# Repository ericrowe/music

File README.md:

# Music Fabrication & Band Prop Engineering Repository

This umbrella repository supports independent music fabrication, 3D parametric CAD modeling, and controlled engineering documentation for musical instruments, accessories, and competitive field marching band props.

---

## 🎺 Subprojects Overview

### 1. Pine Creek High School Marching Band (PCHSMB)

Prop engineering, fabrication guides, and volunteer field operations for the Pine Creek High School Marching Band (Colorado Springs, CO):

| Subproject | Description | Key Deliverables & Manuals |
|---|---|---|
| [**2026 Production: *Continuum***](PCHSMB/2026%20Continuum/) | Master competition day field operations guide coordinating all 35 props (16 Duck Blinds, 11 Backdrops, 4 Stages + 4 Staircases). | • [`Continuum_2026_Prop_Operations_Guide.pdf`](PCHSMB/2026%20Continuum/Continuum_2026_Prop_Operations_Guide.pdf) (15 pp)<br>• NFHS High School & NCAA College field coordinate maps & pocket cards<br>• Wind safety NO-GO threshold (>20 mph) & operational weather briefings |
| [**Rolling Backdrops**](PCHSMB/_Backdrop/) | 11 modular 10 ft H × 8 ft W visual displays on heavy-duty 2x4 rolling carts with 60" mid rails and 3/4" iron wing ballast posts. | • [`Backdrop_Assembly_Guide.pdf`](PCHSMB/_Backdrop/docs/Backdrop_Assembly_Guide.pdf) (Release v0 (D9), 28 pp)<br>• Semicircular wind relief flaps ($R=4.0"$, $8" \times 4"$, 8-flap 3-2-3 primary layout)<br>• Frame CAD, drill alignment jigs & substrate trade study (`TS-BDP-2026-02`) |
| [**Sideline Screens ("Duck Blinds")**](PCHSMB/_Sideline%20Screen/) | 16 folding 4 ft H × 8 ft W front sideline concealers in 3/4" EMT conduit; folds coplanar to $< 2.0"$. | • [`Sideline_Screen_Duck_Blind_Build_Instructions.pdf`](PCHSMB/_Sideline%20Screen/docs/Sideline_Screen_Duck_Blind_Build_Instructions.pdf) (Release v0 (D34), 27 pp)<br>• Two-Student Direct Carry protocol (zero carts)<br>• Semicircular wind relief flaps ($R=4.0"$, 6 flaps) & universal corner protectors |
| [**Performance Stages & Staircases**](PCHSMB/_Stages/) | 4 modular rolling performance stages (8 half-units) and 4 mobile staircases with flush 6.0" inter-section gap bridges. | • [`Stage_Platform_Build_Instructions.pdf`](PCHSMB/_Stages/docs/Stage_Platform_Build_Instructions.pdf) (Release v0 (D1), 11 pp)<br>• 6.0" Inter-Section Gap Bridge Analysis (`TR-STG-2026-01`)<br>• Shaded Lighting Scaffolding Pavilion Trade Study (`TS-STG-2026-02`) |
| [**Universal Field Prop Lighting Platform**](PCHSMB/_Lighting%20Controller/) | Enduring, show-agnostic 915 MHz Sub-GHz wireless lighting control ecosystem (Synapse Pit Master Console & Peripheral Prop Nodes). | • Systems Requirements ([`REQUIREMENTS.md`](PCHSMB/_Lighting%20Controller/docs/REQUIREMENTS.md)) & Schematics ([`CARRIER_BOARD_SCHEMATICS.md`](PCHSMB/_Lighting%20Controller/docs/CARRIER_BOARD_SCHEMATICS.md))<br>• KiCad carrier boards, Pilot & 30-Prop BOM Guides, & zero-code CSV show workflow<br>• HTML5 Field Show Simulator & Prop Power Calculator |
| [**Technical Reports & Concept Planning**](PCHSMB/TECHNICAL_REPORTS_REGISTRY.md) | Master engineering registry (`TR`/`TS`/`SPEC`/`DIR`), 2027 Prop Ecosystem Executive Menu, and Director's Briefing Deck. | • [`TECHNICAL_REPORTS_REGISTRY.md`](PCHSMB/TECHNICAL_REPORTS_REGISTRY.md)<br>• [`PCHSMB/docs/`](PCHSMB/docs/) |
| **Legacy & Research** | Historical show props, mechanical flag launchers, and kinetic mechanisms. | • [`PCHSMB/2023 Firebird/`](PCHSMB/2023%20Firebird/), [`2024 Medusa/`](PCHSMB/2024%20Medusa/), [`2025 Valkyrie/`](PCHSMB/2025%20Valkyrie/)<br>• [`PCHSMB/Experiments/Flag Launcher/`](PCHSMB/Experiments/Flag%20Launcher/) & [`Kinetics/`](PCHSMB/Experiments/Kinetics/) |

---

### 2. Instrument Accessories & Workshop Projects

| Project | Description | Primary Materials / Formats |
|---|---|---|
| [**Standcessories**](Standcessories/) | Stand-mounted accessories (mute holders, pencil clips, tablet mounts) engineered for Manhasset #48 music stands. | FreeCAD (`.FCStd`), 3MF slicer files, Black PETG/PLA |
| [**Trumpet**](Trumpet/) | Trumpet mutes (straight, cup, practice), Jo-Ral mute replacement caps, mouthpiece holders, and lyres. | FreeCAD (`.FCStd`), 3MF slicer files, 3D printed acoustics |
| [**Flutes**](Flutes/) | Wall mounts, display fixtures, and stands for Native American and concert flutes. | FreeCAD (`.FCStd`), 3MF slicer files |
| [**Baritone**](Baritone/) & [**Horn**](Horn/) | Replacement valve finger buttons and instrument-mounted pencil clips. | FreeCAD (`.FCStd`), 3MF slicer files, STL meshes |
| [**Luggage Tags**](Luggage%20Tags/) | Personalized, durable instrument case luggage tags. | 3D printed TPU (flexible) |

---

## 📐 Repository Standards & AI Agent Guidelines

Authoritative engineering and documentation rules are codified in:
- [**`AGENTS.md`**](AGENTS.md): Universal cross-agent architecture, document registries, and cross-project synchronization rules.
- [**`GEMINI.md`**](GEMINI.md): Antigravity / Gemini CLI adapter.

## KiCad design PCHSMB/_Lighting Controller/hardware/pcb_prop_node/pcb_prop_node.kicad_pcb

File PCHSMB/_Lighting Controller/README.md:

# PCHSMB Universal Field Prop Lighting Control System

The **PCHSMB Universal Field Prop Lighting Control System** is an enduring, show-agnostic field electronics and wireless lighting platform engineered for the Pine Creek High School Marching Band. It replaces single-use, ad-hoc wiring rigs with a standardized, modular infrastructure capable of synchronizing dynamic visual illumination across up to 64 independent field props (including rolling backdrops, sideline screens, performance stages, soloist platforms, kinetic props, and field tarps) on a regulation outdoor football stadium.

The system is decoupled from any single competitive production. Future band productions can completely reprogram all lighting cues, color schemes, dynamic chases, groupings, and downbeat triggers each season **without requiring software development, command-line tools, firmware compilation, or artificial intelligence prompting**.

---

## 1. System Architecture & Signal Flow

```
===================================================================================================
                                      SYSTEM SIGNAL FLOW & TOPOLOGY
===================================================================================================

[NON-TECHNICAL SHOW AUTHORING]
Band Directors & Students edit show_cues.csv in Microsoft Excel / Google Sheets
                                  │
                                  ▼
[ZERO-CODE SHOW DEPLOYMENT]
  Method A: Drag-and-drop onto Synapse USB Drive ("PCHSMB_LIGHT")
  Method B: Connect smartphone/tablet to Synapse Wi-Fi Portal (http://192.168.4.1/)
                                  │
                                  ▼
┌─────────────────────────────────────────────────────────────────────────────────────────────────┐
│ SYNAPSE PIT MASTER CONSOLE (PCB-SYNAPSE-V1)                                                    │
│ • Front-Ensemble Tabletop Console (Pit Cart Accessory Rail Mount)                               │
│ • 16x 16mm Rugged Momentary Pushbuttons (Screw-Clamp Terminals, Zero Solder)                    │
│ • Dedicated Emergency Blackout E-Stop (Hardware Priority Interrupt)                            │
│ • Rotary Parameter Encoder + 128x64 Sunlight-Readable OLED Status Display                       │
│ • 3.5mm Isolated SMPTE LTC / Audio Click Track Line-In                                         │
│ • Dual-Source OR-ed Power Bus (5V USB + 7-18V Auxiliary DC)                                     │
│ • 902–928 MHz Sub-GHz ISM Broadcast Master (Semtech SX1262 Transceiver, RP-SMA Antenna)         │
└────────────────────────────────────────────────┬────────────────────────────────────────────────┘
                                                 │
                                                 │ 902–928 MHz Wireless Broadcast Link (Clock Sync & Cue Downbeats)
                                                 │ Master Millisecond Timecode Heartbeat + Event Triggers
                                                 │ Phase-Lock Jitter ≤ 2.0 ms | Slant Range ≥ 150 m | Zero Central Streaming
                                                 │
                                                 ▼
┌─────────────────────────────────────────────────────────────────────────────────────────────────┐
│ PERIPHERAL PROP RECEIVER & LED DRIVER (PCB-PROP-NODE-V1) [FLEET: 1 TO 256 PROPS]               │
│ • Deployed Inside Field Props (Backdrops, Sideline Screens, Soloist Platforms, Star Tarps)     │
│ • Standard Commercial Tool Battery Input (Milwaukee M18 / DeWalt 20V, 15V–21V DC)              │
│ • High-Efficiency 5.0V / 8.0A Continuous Synchronous Buck Regulator                            │
│ • Hardware Reverse-Polarity P-FET + Hardware 15.0V Undervoltage Lockout (UVLO)                  │
│ • 8-Bit Hardware DIP Switch Bank (Unique Device Hardware Serial ID 0–255 / 0x00–0xFF)           │
│ • Distributed Timeline Engine: Autonomous Flash Cues on 40 MHz Quartz Oscillator Time           │
│ • Loss-of-Signal Immunity: Uninterrupted local cue execution (crystal drift < 15ms over 12 min) │
│ • Spare Remap: Wi-Fi OTA off-field or < 100ms emergency 915 MHz profile push from Synapse     │
│ • Quad-Channel 5.0V CMOS Level Shifter (74AHCT125) with 33Ω Transmission Line Resistors        │
└────────────────────────────────────────────────┬────────────────────────────────────────────────┘
                                                 │
                                                 ▼ 4x High-Speed Damped Parallel Data Lines (5V)
┌─────────────────────────────────────────────────────────────────────────────────────────────────┐
│ PROP LED FIXTURES & SURFACE ARRAYS                                                             │
│ Channel 1: Primary Outline / Perimeter Rail Extrusion (WS2812B / SK6812 / APA102)               │
│ Channel 2: Secondary Accent / Kinetic Graphic Trim                                             │
│ Channel 3: Downward Stage Deck Wash / Soloist Core Luminaire                                   │
│ Channel 4: Ground Runner / Ancillary Ribbon / Auxiliary Luminaire                              │
└─────────────────────────────────────────────────────────────────────────────────────────────────┘
===================================================================================================
```

---

## 2. Subsystem Directory Structure

```
_Lighting Controller/
├── IDEAS.md                              # Project Inbox & Engineering Backlog (HitL Workflow)
├── docs/                                 # Controlled Documentation & Schematics
│   ├── REQUIREMENTS.md                   # Authoritative Systems Requirements (INCOSE / ISO 29148)
│   ├── CARRIER_BOARD_SCHEMATICS.md       # Electrical Schematics, Pinouts & Netlists
│   ├── Lighting_Controller_Pilot_Build_BOM.pdf   # 1 Synapse + 3 Peripherals Pilot Procurement Guide
│   ├── Carrier_Board_BOM_Purchasing_Guide.pdf    # Full Fleet 30-Prop Purchasing Schedule
│   ├── project.json                      # Controlled Document Build Manifest
│   ├── AGENTS.md                         # Subproject Engineering Instructions
│   └── images/                           # High-Resolution 3D PCB Previews & Visuals
│
├── hardware/                             # Master CAD, KiCad & PCB Fabrication
│   ├── pcb_synapse_controller/           # Synapse Carrier Board KiCad Project (ERC/DRC 0 Errors)
│   ├── pcb_prop_node/                    # Prop Node Carrier Board KiCad Project (ERC/DRC 0 Errors)
│   └── build_kicad_carrier_boards.py     # Pure-Python Parametric KiCad Generator & DRC Runner
│
├── firmware/                             # Microcontroller Software & Protocol Stack
│   └── README.md                         # Dual-Core ESP32-S3 Tasking, 915 MHz Framing & DMA Engine
│
└── software/                             # Show Reprogramming & Zero-Code Authoring Suite
    ├── README.md                         # Non-Technical Authoring & Ingestion Guide
    ├── show_cues_template.csv            # Master CSV Show Cue Template (Excel / Sheets Friendly)
    └── PCHSMB_Show_Simulator.html        # Interactive Zero-Install HTML5 Field Visualizer & Validator
```

---

## 3. Hardware Subsystem Specifications

### A. Synapse Pit Master Console (`PCB-SYNAPSE-V1`)
* **Form Factor:** Compact tabletop aluminum console clamped to a front-ensemble keyboard or percussion rack rail on the front sideline.
* **Operator Interface:** 16 discrete, heavy-duty $16\,\text{mm}$ IP67 metal momentary pushbuttons arranged for two-handed fingertip triggering by a gloved student musician.
* **Zero-Solder Field Wiring:** All 16 pushbuttons connect to the carrier board via high-retention $5.08\,\text{mm}$ screw-clamp terminal blocks (`J5` and `J6`).
* **Emergency Blackout (E-Stop):** Dedicated 2-pin screw terminal (`J7`) routed to a high-priority hardware interrupt, transmitting a preemptive visual blackout packet across the entire field in $T \le 5.0\,\text{ms}$.
* **Navigation & Feedback:** 24-detent continuous rotary encoder with push switch, paired with a $128 \times 64$ sunlight-readable monochrome OLED display.
* **Audio Synchronization:** Isolated $3.5\,\text{mm}$ line-in jack for SMPTE LTC timecode or front ensemble audio click track pulse detection.
* **Dual Power OR-ing:** Operates seamlessly from either $5.0\,\text{V}$ USB or auxiliary $7.0\,\text{V}\text{–}18.0\,\text{V}$ DC with zero brownout or MCU reset when switching sources.
* **Wireless Transceiver:** Heltec V3 ESP32-S3 module with Semtech SX1262 LoRa/FSK transceiver, outputting $+22\,\text{dBm}$ into a chassis-mounted RP-SMA whip antenna.

### B. Peripheral Prop Receiver & Driver Node (`PCB-PROP-NODE-V1`)
* **Deployment:** Sealed inside weather-resistant 3D-printed enclosures mounted to field props (Rolling Backdrops, Sideline Screens, Soloist Stages, Star Tarps).
* **Power Source:** Universal commercial $18\,\text{V}$ tool battery packs (DeWalt 20V Max / Milwaukee M18, $15.0\,\text{V}\text{–}21.0\,\text{V}$ DC).
* **Step-Down Power Conversion:** Finned waterproof synchronous buck regulator delivering $5.0\,\text{V} \pm 0.15\,\text{V}$ DC regulated at up to $20.0\,\text{A}$ continuous ($100\,\text{W}$, $\ge 95\%$ efficiency).
* **Battery Protection & Safety:**
  - Hardware P-channel power MOSFET reverse-polarity protection ($V_{\text{drop}} \le 40\,\text{mV}$, survives $-24\,\text{V}$ DC indefinitely).
  - Hardware Undervoltage Lockout (UVLO) disconnecting load at $V_{\text{bat}} \le 14.8\,\text{V}$ to prevent permanent lithium cell damage.
* **Parallel Multi-Zone Driving:** Quad $5.0\,\text{V}$ CMOS level-shifted push-pull channels (`74AHCT125`) with $33\,\Omega$ series transmission line resistors, driving up to $5.0\,\text{m}$ of external cable without edge ringing.
* **8-Bit Hardware DIP Switch Bank (`SW1`):** 8-position slide DIP switch providing 256 unique hardware device serial numbers (`0`–`255` / `0x00`–`0xFF`). Decouples physical hardware serial from software show configuration.

### C. Distributed Autonomous Timeline & Quartz Phase-Locking Architecture
* **Autonomous Local Show Engines:** Each prop node functions as an independent animation engine executing its scheduled cue timeline from onboard SPI flash memory. Every unit runs identical precompiled firmware, but executes its unique assigned timeline profile (e.g., Unit 4 triggers Cue 3 at $18.43\,\text{s}$ with a 2-second cyan bloom, while Unit 12 triggers Cue 3 at $20.15\,\text{s}$ with a radial chase).
* **915 MHz Millisecond Clock-Sync Heartbeat:** The Sub-GHz broadcast link does **not** stream raw pixel frames and is **not** a single point of failure. It periodically transmits an unacknowledged elapsed millisecond timecode packet (`uint32_t master_ms`).
* **Loss-of-Signal Immunity:** Local prop timing is clocked by the Heltec V3's onboard $40\,\text{MHz}$ quartz crystal oscillator. If RF communication is momentarily shadowed by stadium structures or drops out entirely, **animations do not freeze or halt**. The node continues executing its timeline on quartz crystal time with $< 15\,\text{ms}$ total drift over a 12-minute field show. When the 915 MHz signal is re-established, a Phase-Locked Loop (PLL) slews the local millisecond clock seamlessly back into sub-frame synchronization.
* **Spare Unit Replacement & Re-mapping Workflow:** If a field prop (e.g., Unit 4) suffers mechanical or electrical damage on the sideline and spare Unit 18 is deployed:
  1. *Off-Field / Rehearsal Re-mapping:* Connect to Unit 18 via Wi-Fi OTA portal (or local staging router) and select "Assign Profile: Prop 4". The complete 272-byte timeline profile is flashed to Unit 18 in $< 2.0\,\text{s}$.
  2. *On-Field Emergency Re-mapping:* From the Synapse pit master console OLED rotary menu, select `SPARE REMAP: HW18 -> PROP 4`. Synapse broadcasts a high-priority 915 MHz configuration packet re-mapping Unit 18's DIP serial to Prop 4's timeline profile in $< 100\,\text{ms}$ without requiring laptops, Wi-Fi networks, or physical disassembly.

---

## 4. The Zero-Code Show Reprogramming Suite

High school marching band staff change from season to season. The PCHSMB platform enforces a strict **Zero-Software & Zero-AI Reprogramming Mandate** (**`REQ-SW-01`**):

1. **Spreadsheet Authoring:** Directors and visual coordinators edit cues in [`software/show_cues_template.csv`](software/show_cues_template.csv) using **Microsoft Excel, Google Sheets, or Apple Numbers**.
2. **Instant Browser Testing:** Double-clicking [`software/PCHSMB_Show_Simulator.html`](software/PCHSMB_Show_Simulator.html) opens an interactive 2D football field simulator in any browser. Users drag and drop their CSV file to validate syntax and test cues 1–16 on a virtual field grid in real-time.
3. **Plug-and-Play Loading:**
   - **Method A (USB Flash Drive):** Connect Synapse to any computer via USB-C. Drag and drop `show_cues.csv` onto the `PCHSMB_LIGHT` drive. Synapse validates the file upon eject and flashes its memory.
   - **Method B (Rehearsal Web Engine & LoRa-Orchestrated Wi-Fi):** During practices on shore power, an optional integrated Raspberry Pi and travel router host a full browser dashboard, waking up fleet prop Wi-Fi on demand via a LoRa command packet for zero-touch Over-The-Air show updates across all 30+ field props (see [`IDEAS.md`](IDEAS.md) — Idea 001).
4. **Error Protection:** Typos in Excel generate an immediate plain-English report (`error_log.txt` and OLED notification) pinpointing the exact row and column without crashing the system.

---

## 5. Procurement & Budget Schedules

| Scope | Assemblies Included | Estimated Total Cost | Status / Procurement Guide |
|---|---|:---:|---|
| **Pilot Bench Kit** | 1 Synapse Master + 3 Prop Nodes (4-Node Test Mesh) | **$332.25** | [View Pilot Build BOM (PDF)](docs/Lighting_Controller_Pilot_Build_BOM.pdf) |
| **Full Fleet Expansion** | 30 Prop Nodes (Fleet Backdrops, Screens, Stages) | **~$2,346.80** | [View Fleet Purchasing Guide (PDF)](docs/Carrier_Board_BOM_Purchasing_Guide.pdf) |

All components are standard, commercial off-the-shelf (COTS) parts verified in-stock at Digi-Key, Amazon, and JLCPCB. Enclosures are custom 3D-printed in shop (PETG/ASA). Antennas and cables are bundled with the Heltec ESP32-S3 modules.

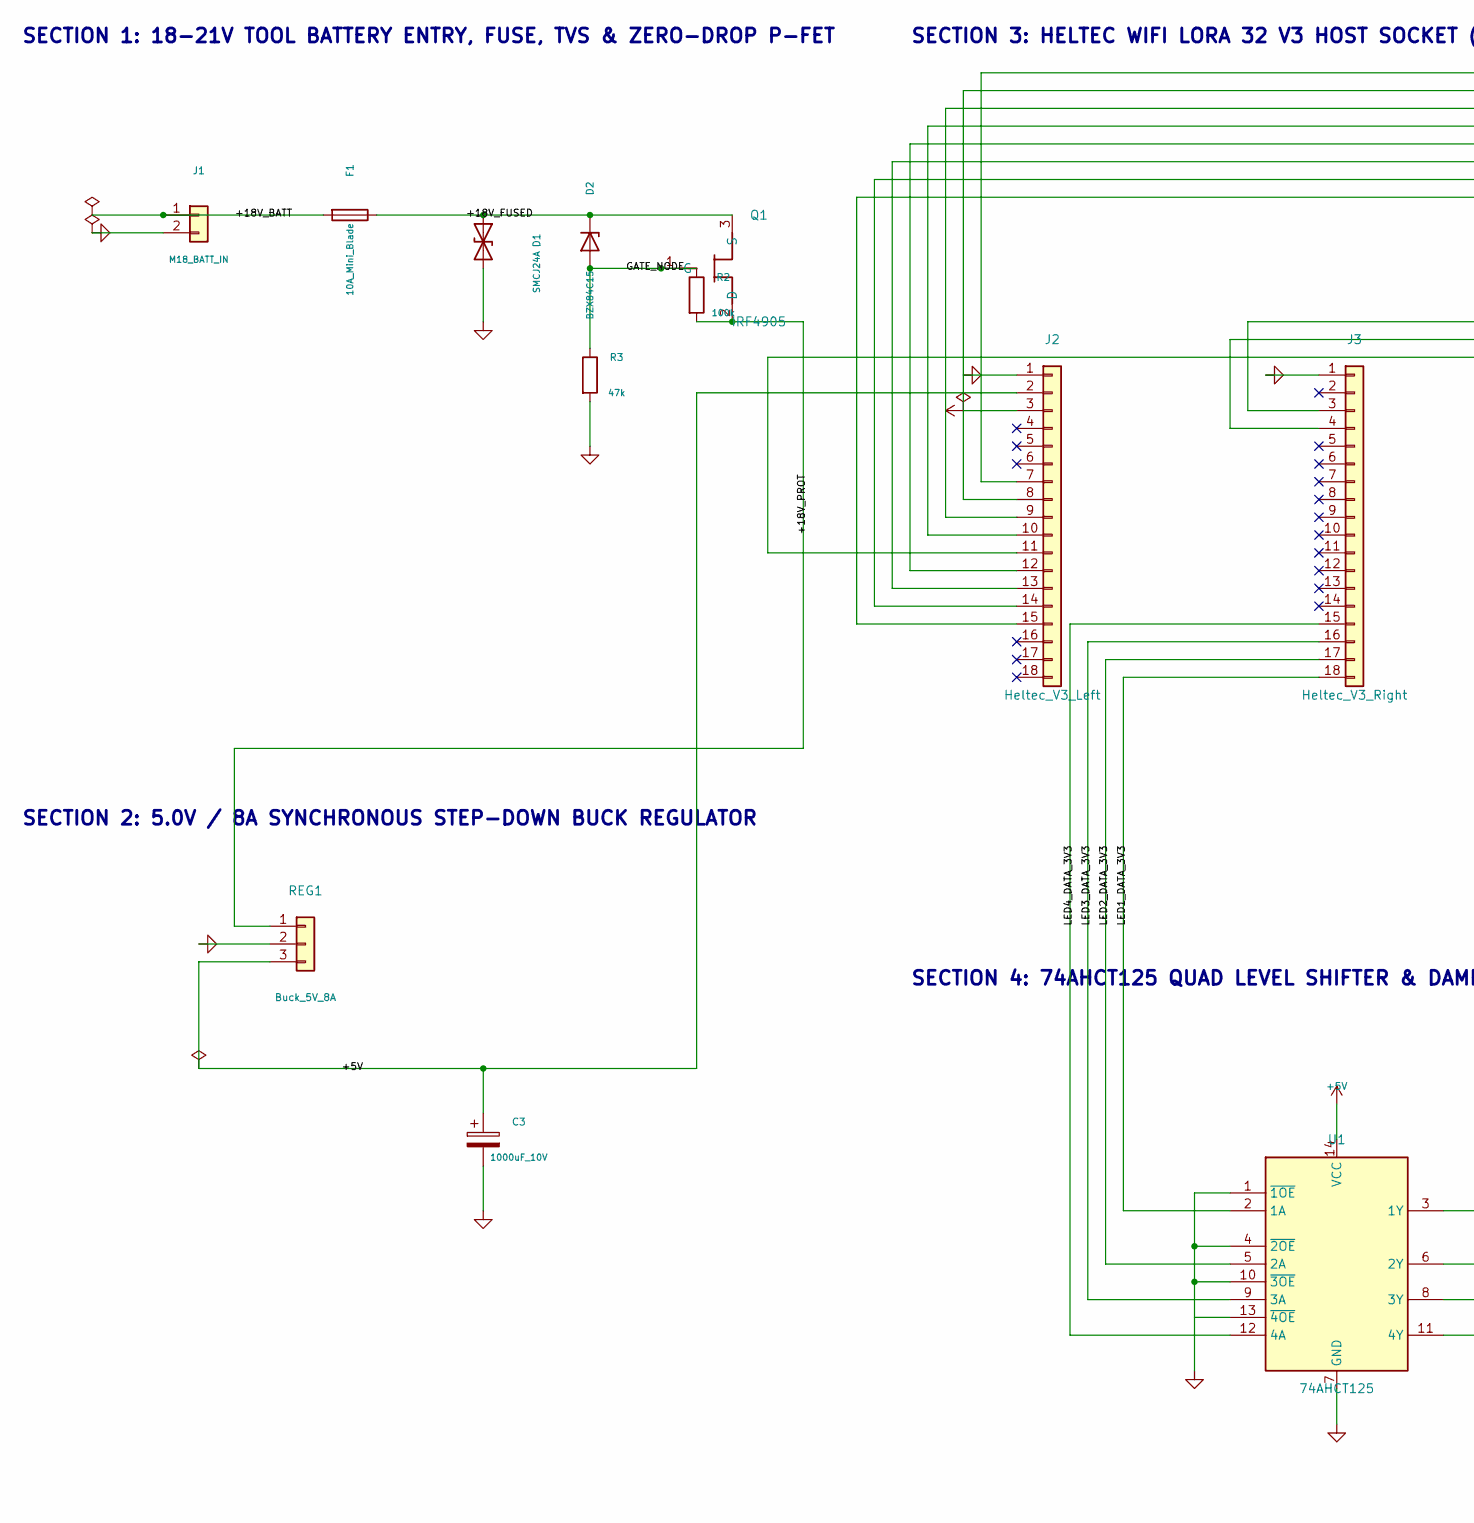
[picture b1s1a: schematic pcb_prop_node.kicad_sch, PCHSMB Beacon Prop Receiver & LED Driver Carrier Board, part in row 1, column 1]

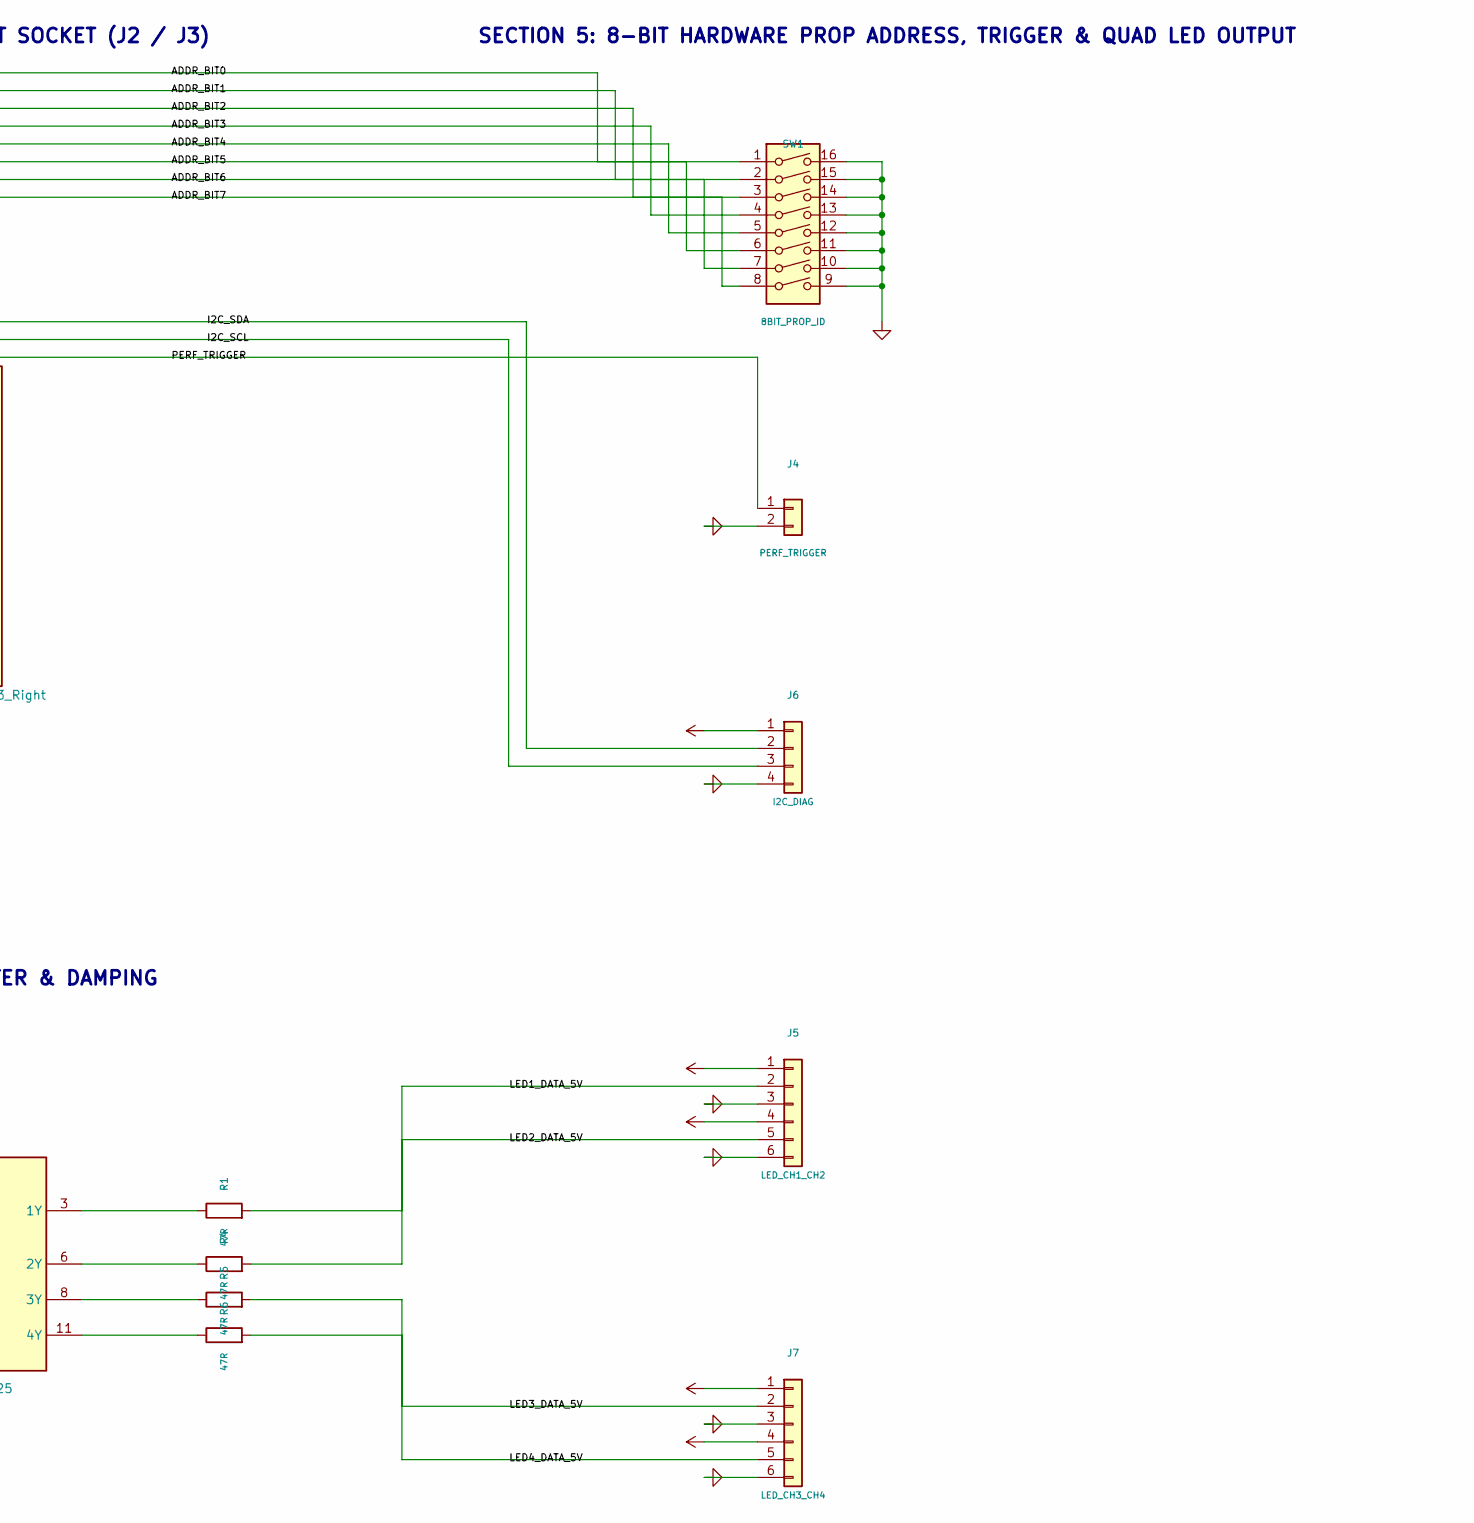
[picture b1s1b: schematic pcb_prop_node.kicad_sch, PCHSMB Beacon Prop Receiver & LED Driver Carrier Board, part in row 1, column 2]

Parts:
C3: 1000uF_10V; CP_Radial_D10.0mm_P5.00mm
D1: SMCJ24A; D_SMC
D2: BZX84C15; SOT-23
F1: 10A_Mini_Blade; Fuseholder_Blade_Mini_Keystone_3568
J1: M18_BATT_IN; PhoenixContact_MSTBA_2,5_2-G-5,08_1x02_P5.08mm_Horizontal
J2: Heltec_V3_Left; PinSocket_1x18_P2.54mm_Vertical
J3: Heltec_V3_Right; PinSocket_1x18_P2.54mm_Vertical
J4: PERF_TRIGGER; PhoenixContact_MSTBA_2,5_2-G-5,08_1x02_P5.08mm_Horizontal
J5: LED_CH1_CH2; PhoenixContact_MSTBA_2,5_6-G-5,08_1x06_P5.08mm_Horizontal
J6: I2C_DIAG; PinHeader_1x04_P2.54mm_Vertical
J7: LED_CH3_CH4; PhoenixContact_MSTBA_2,5_6-G-5,08_1x06_P5.08mm_Horizontal
Q1: IRF4905; TO-220-3_Vertical
R1, R4, R5, R6: 47R; R_0805_2012Metric
R2: 100k; R_0805_2012Metric
R3: 47k; R_0805_2012Metric
REG1: Buck_5V_8A; TerminalBlock_Phoenix_MKDS-1,5-3-5.08_1x03_P5.08mm_Horizont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
SW1: 8BIT_PROP_ID; SW_DIP_SPSTx08_Slide_6.7x21.88mm_W7.62mm_P2.54mm_LowProfile
U1: 74AHCT125; SOIC-14_3.9x8.7mm_P1.27mm

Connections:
/+18V_FUSED: D1.1 (A1), D2.1 (K), F1.1, Q1.3 (S)
/+18V_PROT: Q1.2 (D), R2.2, REG1.1
/ADDR_BIT0: J2.7, SW1.1
/ADDR_BIT2: J2.9, SW1.3
/ADDR_BIT3: J2.10, SW1.4
/ADDR_BIT4: J2.12, SW1.5
/ADDR_BIT5: J2.13, SW1.6
/ADDR_BIT6: J2.14, SW1.7
/ADDR_BIT7: J2.15, SW1.8
/GATE_NODE: D2.2 (A), Q1.1 (G), R2.1, R3.1
/I2C_SCL: J3.4, J6.3
/I2C_SDA: J3.3, J6.2
/LED1_DATA_3V3: J3.18, U1.2 (1A)
/LED1_DATA_5V: J5.2, R1.2
/LED2_DATA_3V3: J3.17, U1.5 (2A)
/LED2_DATA_5V: J5.5, R4.2
/LED3_DATA_3V3: J3.16, U1.9 (3A)
/LED3_DATA_5V: J7.2, R5.2
/LED4_DATA_3V3: J3.15, U1.12 (4A)
/LED4_DATA_5V: J7.5, R6.2
/PERF_TRIGGER: J2.11, J4.1
unnamed: R1.1, U1.3 (1Y)
unnamed: R4.1, U1.6 (2Y)
unnamed: R5.1, U1.8 (3Y)
unnamed: R6.1, U1.11 (4Y)

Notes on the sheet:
SECTION 1: 18-21V TOOL BATTERY ENTRY, FUSE, TVS & ZERO-DROP P-FET
SECTION 2: 5.0V / 8A SYNCHRONOUS STEP-DOWN BUCK REGULATOR
SECTION 3: HELTEC WIFI LORA 32 V3 HOST SOCKET (J2 / J3)
SECTION 4: 74AHCT125 QUAD LEVEL SHIFTER & DAMPING
SECTION 5: 8-BIT HARDWARE PROP ADDRESS, TRIGGER & QUAD LED OUTPUT

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
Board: 2 copper layers, 25 parts (0 on the bottom side), 30 nets, no tracks yet.

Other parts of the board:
H1, H2, H3, H4: MountingHole_3.2mm_M3

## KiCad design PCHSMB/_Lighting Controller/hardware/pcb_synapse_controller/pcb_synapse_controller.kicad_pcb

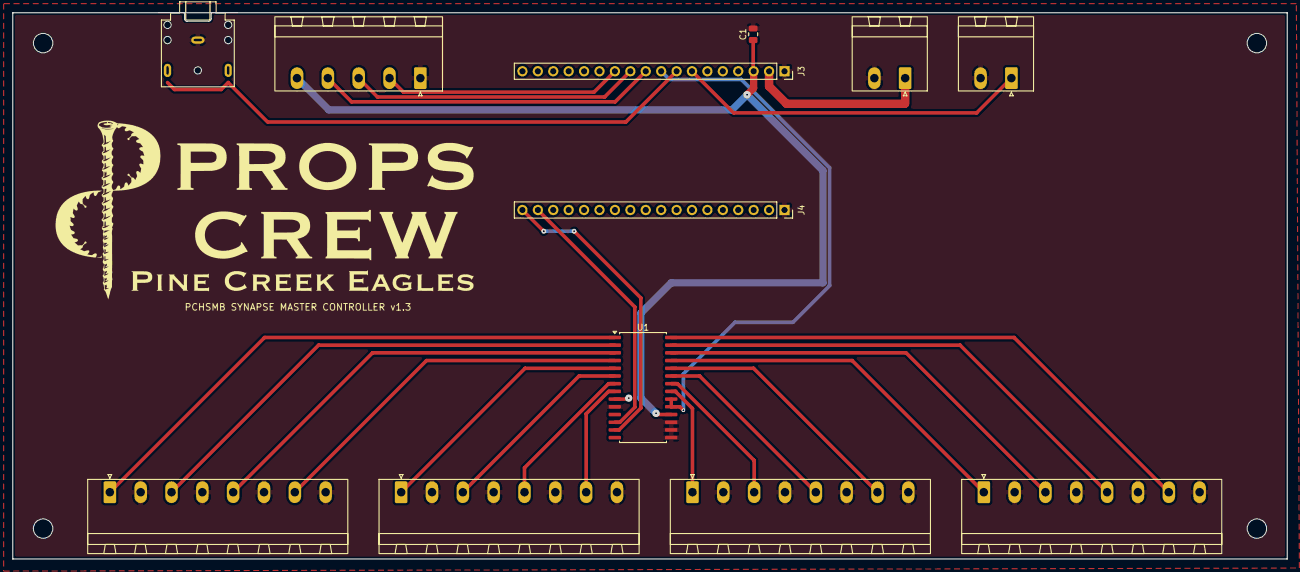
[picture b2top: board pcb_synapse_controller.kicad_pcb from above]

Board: 2 copper layers, 210.0 x 90.0 mm, 16 parts (0 on the bottom side), 27 nets.

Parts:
C1: 100nF; C_0805_2012Metric
H1, H2, H3, H4: MountingHole_3.2mm_M3
J1: 3.5mm_Audio_In; Jack_3.5mm_CUI_SJ1-3523N_Horizontal
J2: 5V_DC_IN; PhoenixContact_MSTBA_2,5_2-G-5,08_1x02_P5.08mm_Horizontal
J3: Heltec_V3_Left; PinSocket_1x18_P2.54mm_Vertical
J4: Heltec_V3_Right; PinSocket_1x18_P2.54mm_Vertical
J5: Buttons_1_to_4; PhoenixContact_MSTBA_2,5_8-G-5,08_1x08_P5.08mm_Horizontal
J6: Buttons_5_to_8; PhoenixContact_MSTBA_2,5_8-G-5,08_1x08_P5.08mm_Horizontal
J7: Blackout_E_Stop; PhoenixContact_MSTBA_2,5_2-G-5,08_1x02_P5.08mm_Horizontal
J8: Buttons_9_to_12; PhoenixContact_MSTBA_2,5_8-G-5,08_1x08_P5.08mm_Horizontal
J9: Buttons_13_to_16; PhoenixContact_MSTBA_2,5_8-G-5,08_1x08_P5.08mm_Horizontal
J10: Rotary_Encoder; PhoenixContact_MSTBA_2,5_5-G-5,08_1x05_P5.08mm_Horizontal
U1: MCP23017; SOIC-28W_7.5x17.9mm_P1.27mm

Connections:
+3V3: C1.1, J3.3, J10.5, U1.9 (V_{DD}), U1.18 (~RESET)
+5V: J2.1, J3.2
/AUDIO_IN: J1.R, J1.T, J3.8
/BLACKOUT: J3.7, J7.1
/BTN_01: J5.1, U1.1 (GPB0)
/BTN_02: J5.3, U1.2 (GPB1)
/BTN_03: J5.5, U1.3 (GPB2)
/BTN_04: J5.7, U1.4 (GPB3)
/BTN_05: J6.1, U1.5 (GPB4)
/BTN_06: J6.3, U1.6 (GPB5)
/BTN_07: J6.5, U1.7 (GPB6)
/BTN_08: J6.7, U1.8 (GPB7)
/BTN_09: J8.1, U1.21 (GPA0)
/BTN_10: J8.3, U1.22 (GPA1)
/BTN_11: J8.5, U1.23 (GPA2)
/BTN_12: J8.7, U1.24 (GPA3)
/BTN_13: J9.1, U1.25 (GPA4)
/BTN_14: J9.3, U1.26 (GPA5)
/BTN_15: J9.5, U1.27 (GPA6)
/BTN_16: J9.7, U1.28 (GPA7)
/ENC_A: J3.10, J10.4
/ENC_B: J3.11, J10.3
/ENC_SW: J3.12, J10.2
/I2C_SCL: J4.17, U1.12 (SCK)
/I2C_SDA: J4.18, U1.13 (SDA)
/MCP_INT: J3.9, U1.19 (INTB), U1.20 (INTA)
GND: C1.2, J1.S, J2.2, J3.1, J4.1, J5.2, J5.4, J5.6, J5.8, J6.2, J6.4, J6.6, J6.8, J7.2, J8.2, J8.4, J8.6, J8.8, J9.2, J9.4, J9.6, J9.8, J10.1, U1.10 (V_{SS}), U1.15 (A0), U1.16 (A1), U1.17 (A2)

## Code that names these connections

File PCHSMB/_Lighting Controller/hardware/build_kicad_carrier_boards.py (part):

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    (property "Value" "GND" (at 35.56 83.82 0) (effects (font (size 1 1)) hide))
    (pin "1" (uuid "{uid()}"))
  )''')
    # Pin 1 (BLACKOUT): at (45.72, 81.28) -> wire directly to Heltec J3 Pin 7 at (142.24, 88.90)
    elements.append(f'''  (wire (pts (xy 45.72 81.28) (xy 88.90 81.28)) (stroke (width 0)) (uuid "{uid()}"))''')
    elements.append(f'''  (wire (pts (xy 88.90 81.28) (xy 88.90 88.90)) (stroke (width 0)) (uuid "{uid()}"))''')
    elements.append(f'''  (wire (pts (xy 88.90 88.90) (xy 142.24 88.90)) (stroke (width 0)) (uuid "{uid()}"))''')
    elements.append(f'''  (label "BLACKOUT" (at 63.50 81.28 0) (effects (font (size 1 1))) (uuid "{uid()}"))''')

    # --------------------------------------------------------------------------
    # 3. J10: Rotary Encoder 5-Pin Pluggable at (55.88, 152.40) - Pluggable MSTBA
    # Pin 1: GND
    # Pin 2: ENC_A -> Heltec J3 Pin 10
    # Pin 3: ENC_B -> Heltec J3 Pin 11
    # Pin 4: ENC_SW -> Heltec J3 Pin 12
    # Pin 5: +3V3_SYS (Auxiliary power for optical/illuminated encoders)
    # --------------------------------------------------------------------------
    ex, ey = 55.88, 152.40
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    (pin "1" (uuid "{uid()}"))
  )''')

    # Pin 2 (ENC_A): at (50.80, 149.86) -> wire to Heltec J3 Pin 10 at (142.24, 96.52)
    elements.append(f'''  (wire (pts (xy 50.80 149.86) (xy 43.18 149.86)) (stroke (width 0)) (uuid "{uid()}"))''')
    elements.append(f'''  (wire (pts (xy 43.18 149.86) (xy 43.18 139.70)) (stroke (width 0)) (uuid "{uid()}"))''')
    elements.append(f'''  (wire (pts (xy 43.18 139.70) (xy 96.52 139.70)) (stroke (width 0)) (uuid "{uid()}"))''')
    elements.append(f'''  (wire (pts (xy 96.52 139.70) (xy 96.52 96.52)) (stroke (width 0)) (uuid "{uid()}"))''')
    elements.append(f'''  (wire (pts (xy 96.52 96.52) (xy 142.24 96.52)) (stroke (width 0)) (uuid "{uid()}"))''')
    elements.append(f'''  (label "ENC_A" (at 68.58 139.70 0) (effects (font (size 1 1))) (uuid "{uid()}"))''')

    # Pin 3 (ENC_B): at (50.80, 152.40) -> wire to Heltec J3 Pin 11 at (142.24, 99.06)
    elements.append(f'''  (wire (pts (xy 50.80 152.40) (xy 40.64 152.40)) (stroke (width 0)) (uuid "{uid()}"))''')
    elements.append(f'''  (wire (pts (xy 40.64 152.40) (xy 40.64 142.24)) (stroke (width 0)) (uuid "{uid()}"))''')
    elements.append(f'''  (wire (pts (xy 40.64 142.24) (xy 99.06 142.24)) (stroke (width 0)) (uuid "{uid()}"))''')
    elements.append(f'''  (wire (pts (xy 99.06 142.24) (xy 99.06 99.06)) (stroke (width 0)) (uuid "{uid()}"))''')
    elements.append(f'''  (wire (pts (xy 99.06 99.06) (xy 142.24 99.06)) (stroke (width 0)) (uuid "{uid()}"))''')
    elements.append(f'''  (label "ENC_B" (at 68.58 142.24 0) (effects (font (size 1 1))) (uuid "{uid()}"))''')

    # Pin 4 (ENC_SW): at (50.80, 154.94) -> wire to Heltec J3 Pin 12 at (142.24, 101.60)
    elements.append(f'''  (wire (pts (xy 50.80 154.94) (xy 101.60 154.94)) (stroke (width 0)) (uuid "{uid()}"))''')
    elements.append(f'''  (wire (pts (xy 101.60 154.94) (xy 101.60 101.60)) (stroke (width 0)) (uuid "{uid()}"))''')
    elements.append(f'''  (wire (pts (xy 101.60 101.60) (xy 142.24 101.60)) (stroke (width 0)) (uuid "{uid()}"))''')
    elements.append(f'''  (label "ENC_SW" (at 83.82 154.94 0) (effects (font (size 1 1))) (uuid "{uid()}"))''')

    # Pin 5 (+3V3): at (50.80, 157.48)
    elements.append(f'''  (wire (pts (xy 50.80 157.48) (xy 40.64 157.48)) (stroke (width 0)) (uuid "{uid()}"))''')
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    elements.append(f'''  (wire (pts (xy 66.04 203.20) (xy 91.44 203.20)) (stroke (width 0)) (uuid "{uid()}"))''')
    elements.append(f'''  (wire (pts (xy 91.44 203.20) (xy 91.44 91.44)) (stroke (width 0)) (uuid "{uid()}"))''')
    elements.append(f'''  (wire (pts (xy 91.44 91.44) (xy 142.24 91.44)) (stroke (width 0)) (uuid "{uid()}"))''')
    elements.append(f'''  (label "AUDIO_IN" (at 76.20 203.20 0) (effects (font (size 1 1))) (uuid "{uid()}"))''')

    # --------------------------------------------------------------------------
    # 5. J3: Heltec Left Header (Conn_01x18) at (147.32, 93.98)
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        py = 73.66 + (p - 1) * 2.54
        elements.append(f'''  (no_connect (at 142.24 {py:.2f}) (uuid "{uid()}"))''')

    # Pin 9 (MCP_INT): at (142.24, 93.98) -> wire right to U1 Pins 19 & 20
    elements.append(f'''  (wire (pts (xy 142.24 93.98) (xy 165.10 93.98)) (stroke (width 0)) (uuid "{uid()}"))''')
    elements.append(f'''  (wire (pts (xy 165.10 93.98) (xy 165.10 132.08)) (stroke (width 0)) (uuid "{uid()}"))''')
    elements.append(f'''  (wire (pts (xy 165.10 132.08) (xy 228.60 132.08)) (stroke (width 0)) (uuid "{uid()}"))''')
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    elements.append(f'''  (wire (pts (xy 228.60 99.06) (xy 241.30 99.06)) (stroke (width 0)) (uuid "{uid()}"))''')
    elements.append(f'''  (wire (pts (xy 241.30 99.06) (xy 241.30 96.52)) (stroke (width 0)) (uuid "{uid()}"))''')
    elements.append(f'''  (junction (at 241.30 99.06) (diameter 0) (color 0 0 0 0) (uuid "{uid()}"))''')
    elements.append(f'''  (label "MCP_INT" (at 185.42 132.08 0) (effects (font (size 1 1))) (uuid "{uid()}"))''')

    # --------------------------------------------------------------------------
    # 6. J4: Heltec Right Header (Conn_01x18) at (190.50, 93.98)
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        py = 73.66 + (p - 1) * 2.54
        elements.append(f'''  (no_connect (at 185.42 {py:.2f}) (uuid "{uid()}"))''')

    # Pin 17 (I2C_SCL): at (185.42, 114.30) -> wire to U1 Pin 12 at (241.30, 81.28)
    elements.append(f'''  (wire (pts (xy 185.42 114.30) (xy 215.90 114.30)) (stroke (width 0)) (uuid "{uid()}"))''')
    elements.append(f'''  (wire (pts (xy 215.90 114.30) (xy 215.90 81.28)) (stroke (width 0)) (uuid "{uid()}"))''')
    elements.append(f'''  (wire (pts (xy 215.90 81.28) (xy 241.30 81.28)) (stroke (width 0)) (uuid "{uid()}"))''')
    elements.append(f'''  (label "I2C_SCL" (at 215.90 93.98 90) (effects (font (size 1 1))) (uuid "{uid()}"))''')

    # Pin 18 (I2C_SDA): at (185.42, 116.84) -> wire to U1 Pin 13 at (241.30, 83.82)
    elements.append(f'''  (wire (pts (xy 185.42 116.84) (xy 218.44 116.84)) (stroke (width 0)) (uuid "{uid()}"))''')
    elements.append(f'''  (wire (pts (xy 218.44 116.84) (xy 218.44 83.82)) (stroke (width 0)) (uuid "{uid()}"))''')
    elements.append(f'''  (wire (pts (xy 218.44 83.82) (xy 241.30 83.82)) (stroke (width 0)) (uuid "{uid()}"))''')
    elements.append(f'''  (label "I2C_SDA" (at 218.44 93.98 90) (effects (font (size 1 1))) (uuid "{uid()}"))''')

    # --------------------------------------------------------------------------
    # 7. U1: MCP23017 Expander (SOIC-28W) at (ux=254.00, uy=101.60)
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    elements.append(f'''  (no_connect (at 243.84 {101.60 - 15.24}) (uuid "{uid()}"))''')
    elements.append(f'''  (no_connect (at 243.84 {101.60 - 12.70}) (uuid "{uid()}"))''')

    # Wires: U1 GPA0..7 (pins 21..28 at 266.70) -> BTN_09..16
    for idx in range(8):
        py = 81.28 + idx * 2.54
        btn_num = 9 + idx
        elements.append(f'''  (wire (pts (xy 266.70 {py:.2f}) (xy 274.32 {py:.2f})) (stroke (width 0)) (uuid "{uid()}"))''')
        elements.append(f'''  (label "BTN_{btn_num:02d}" (at 274.32 {py:.2f} 0) (effects (font (size 1 1))) (uuid "{uid()}"))''')

    # Wires: U1 GPB0..7 (pins 1..8 at 266.70) -> BTN_01..08
    for idx in range(8):
        py = 104.14 + idx * 2.54
        btn_num = 1 + idx
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
    # D2 (15V Zener) at (106.68, 54.61) rot=270
    # Cathode Pin 1 at (106.68, 50.80) -> +18V_FUSED
    # Anode Pin 2 at (106.68, 58.42) -> GATE_NODE
    elements.append(f'''  (symbol (lib_id "Device:D_Zener") (at 106.68 54.61 270) (unit 1) (in_bom yes) (on_board yes) (uuid "{sym_uuids['D2']}")
    (property "Reference" "D2" (at 106.68 46.99 0) (effects (font (size 1 1))))
    (property "Value" "BZX84C15" (at 106.68 62.23 0) (effects (font (size 0.9 0.9))))
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
    # Connect D2 Anode Pin 2 to Q1 Gate Pin 1 at (116.84, 58.42)
    elements.append(f'''  (wire (pts (xy 106.68 58.42) (xy 116.84 58.42)) (stroke (width 0)) (uuid "{uid()}"))''')
    elements.append(f'''  (label "GATE_NODE" (at 111.76 58.42 0) (effects (font (size 1 1))) (uuid "{uid()}"))''')

    # R2 (100k Gate Resistor) at (116.84, 76.20)
    # Between +18V_PROT (66.04) and GATE_NODE (58.42)
    # Let's place R2 at (121.92, 62.23) rot=0:
    # Pin 1 at (121.92, 58.42) -> GATE_NODE
    # Pin 2 at (121.92, 66.04) -> +18V_PROT
    elements.append(f'''  (symbol (lib_id "Device:R") (at 121.92 62.23 0) (unit 1) (in_bom yes) (on_board yes) (uuid "{sym_uuids['R2']}")
    (property "Reference" "R2" (at 125.73 59.69 0) (effects (font (size 1 1))))
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    (property "Footprint" "Resistor_SMD:R_0805_2012Metric" (at 121.92 62.23 0) (effects (font (size 1 1)) hide))
    (pin "1" (uuid "{uid()}")) (pin "2" (uuid "{uid()}"))
  )''')
    # Connect R2 Pin 1 to GATE_NODE
    elements.append(f'''  (wire (pts (xy 116.84 58.42) (xy 121.92 58.42)) (stroke (width 0)) (uuid "{uid()}"))''')
    elements.append(f'''  (junction (at 116.84 58.42) (diameter 0) (color 0 0 0 0) (uuid "{uid()}"))''')
    # Connect R2 Pin 2 to Q1 Drain at (127.00, 66.04)
    elements.append(f'''  (wire (pts (xy 121.92 66.04) (xy 127.00 66.04)) (stroke (width 0)) (uuid "{uid()}"))''')
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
